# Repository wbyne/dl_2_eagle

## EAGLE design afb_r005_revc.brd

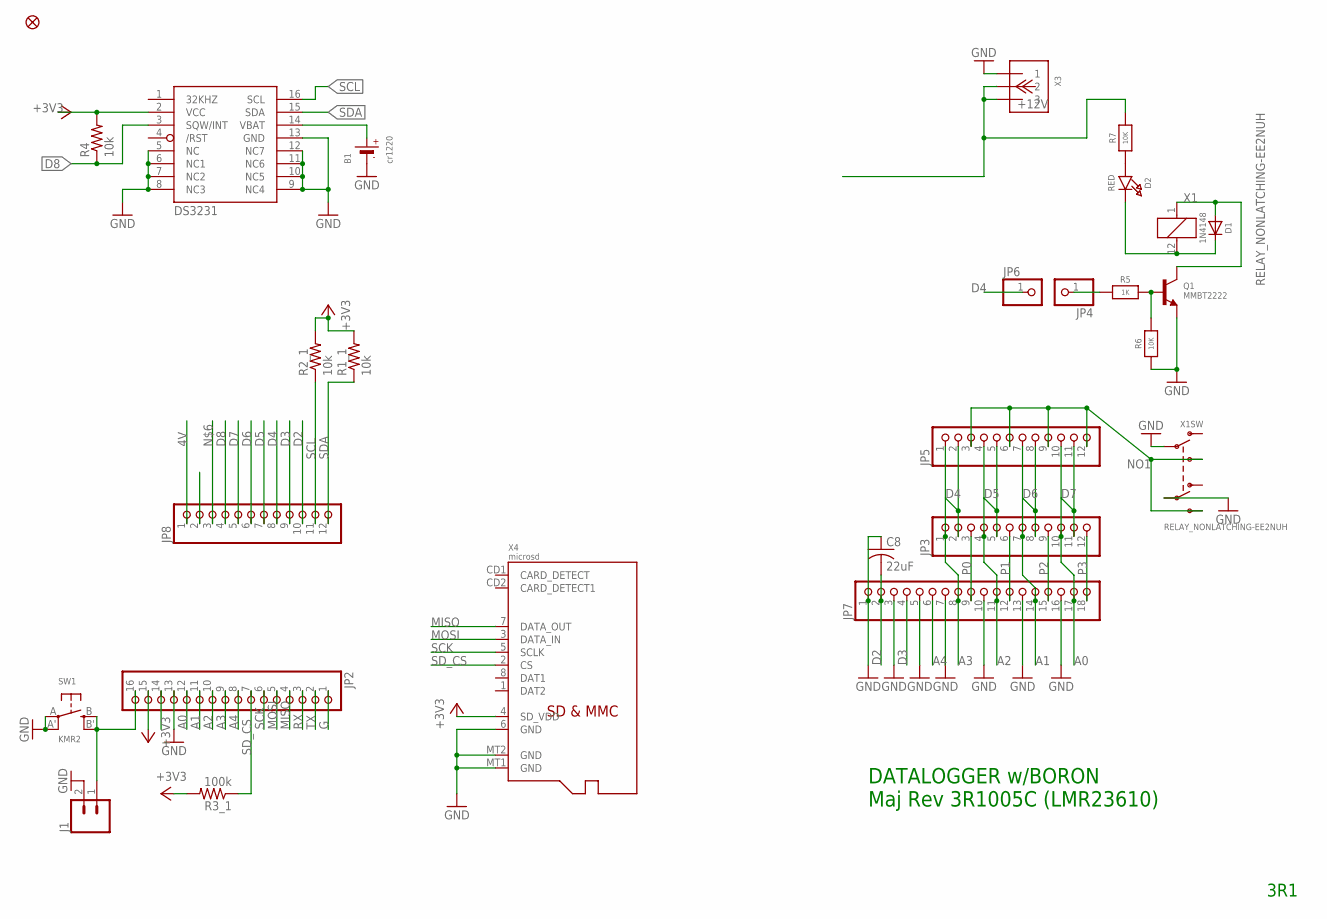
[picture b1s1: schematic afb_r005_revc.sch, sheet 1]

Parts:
B1: cr1220; CR1220-2
C8: 22uF; C0805
D1: 1N4148; SOD-323
D2: RED; CHIPLED_0805_NOOUTLINE
FID1: FIDUCIAL_1MM
IC2: DS3231/SO; SO16W
J1: CONN_02; 1X02
JP2: HEADER-1X16ROUND; 1X16_ROUND
JP3, JP5, JP8: PINHD-1X12-CB; 1X12-CB
JP4, JP6: HEADER-1X1ROUND; 1X01_ROUND
JP7: PINHD-1X18; 1X18
Q1: MMBT2222; SOT23-R
R1_1, R2_1, R4: 10k; R0805
R3_1: 100k; R0805
R5: 1K; 0805-NO
R6, R7: 10K; 0805-NO
SW1: KMR2; BTN_KMR2_4.6X2.8
X1: RELAY_NONLATCHING-EE2NUH; RELAY_EE2_NOLATCH
X3: TERMBLOCK_1X3; TERMBLOCK_1X3-3.5MM
X4: microsd; MICROSD

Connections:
4V: JP8.1; also elsewhere on the board
+3V3: IC2.2 (VCC), JP2.15, R1_1.2, R2_1.2, R3_1.2, R4.2, X4.4 (SD_VDD)
A0: JP2.12, JP3.10, JP5.10, JP7.17
A1: JP2.11, JP3.7, JP5.7, JP7.14
A2: JP2.10, JP3.4, JP5.4, JP7.11
A3: JP2.9, JP3.1, JP5.1, JP7.8
A4: JP2.8, JP7.6
AREF: JP2.14
D2: C8.2, JP7.2, JP8.10
D3: JP7.4, JP8.9
D4: JP3.2, JP5.2, JP6.1, JP8.8
D5: JP3.5, JP5.5, JP8.7
D6: JP3.8, JP5.8, JP8.6
D7: JP3.11, JP5.11, JP8.5
D8: IC2.3 (SQW/INT), JP8.4, R4.1
G: JP2.1
GND: B1.-, C8.1, IC2.5 (NC), IC2.6 (NC1), IC2.7 (NC2), IC2.8 (NC3), IC2.9 (NC4), IC2.10 (NC5), IC2.11 (NC6), IC2.12 (NC7), IC2.13 (GND), J1.2, JP2.13, JP7.1, JP7.3, JP7.5, JP7.7, JP7.10, JP7.13, JP7.16, Q1.2 (E), R6.1, SW1.A, SW1.A' (P1), X1.4 (P2), X1.9 (P1), X3.1, X4.6 (GND), X4.MT1 (GND), X4.MT2 (GND); also elsewhere on the board
MISO: JP2.4, X4.7 (DATA_OUT)
MOSI: JP2.5, X4.3 (DATA_IN)
unnamed: B1.+, IC2.14 (VBAT)
unnamed: D1.A, Q1.3 (C), X1.1
unnamed: D1.C, D2.C, X1.12 (2)
unnamed: Q1.1 (B), R5.2, R6.2
unnamed: JP4.1, R5.1
unnamed: D2.A, R7.1
NO1: JP5.3, JP5.6, JP5.9, JP5.12, X1.5 (S2), X1.8 (S1)
P0: JP3.3, JP7.9
P1: JP3.6, JP7.12
P2: JP3.9, JP7.15
P3: JP3.12, JP7.18
RESET: J1.1, JP2.16, SW1.B (S), SW1.B' (S1)
RX: JP2.3
SCK: JP2.6, X4.5 (SCLK)
SCL: IC2.16 (SCL), JP8.11, R2_1.1
SDA: IC2.15 (SDA), JP8.12, R1_1.1
SD_CS: JP2.7, R3_1.1, X4.2 (CS)
TX: JP2.2
VIN: R7.2, X3.2, X3.3; also elsewhere on the board

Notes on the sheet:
DATALOGGER w/BORON Maj Rev 3R1005C (LMR23610)
3R1

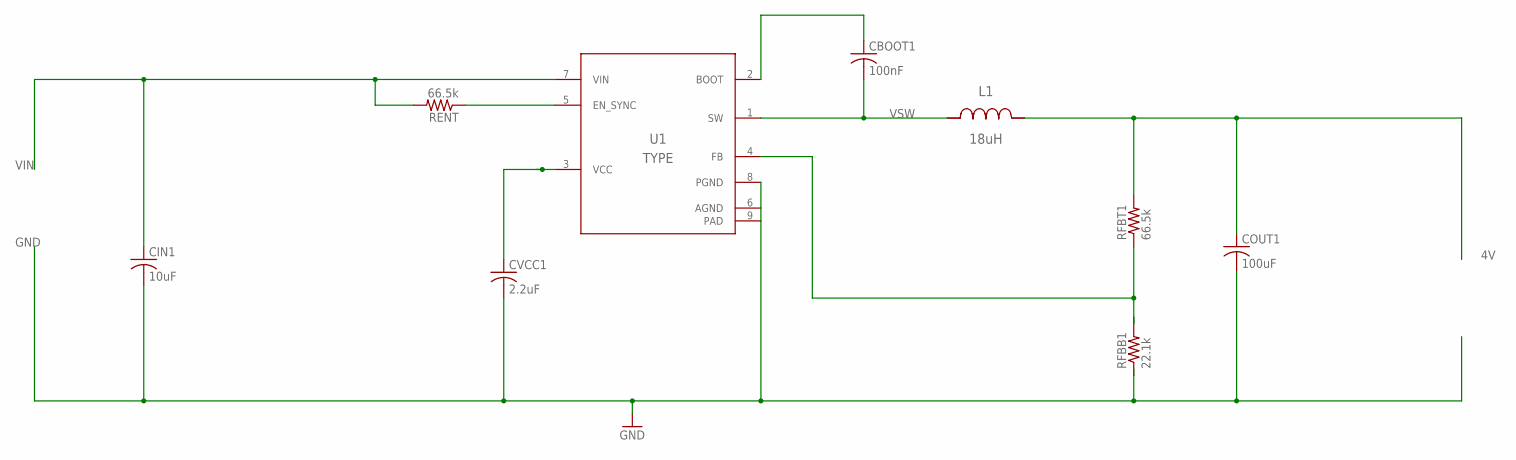
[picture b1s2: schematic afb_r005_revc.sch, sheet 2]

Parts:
CBOOT1: 100nF; C0805
CIN1: 10uF; C0805
COUT1: 100uF; C3216
CVCC1: 2.2uF; C0805
L1: 18uH; IND_NPI54C
RENT: 66.5k; R0805
RFBB1: 22.1k; R0805
RFBT1: 66.5k; R0805
U1: Value; DDA0008E_N

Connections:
3: CVCC1.1, U1.3 (VCC)
4: CBOOT1.1, U1.2 (BOOT)
4V: COUT1.1, L1.2, RFBT1.2; also elsewhere on the board
FB: RFBB1.2, RFBT1.1, U1.4 (FB)
GND: CIN1.2, COUT1.2, CVCC1.2, RFBB1.1, U1.6 (AGND), U1.8 (PGND), U1.9 (PAD); also elsewhere on the board
unnamed: RENT.1, U1.5 (EN_SYNC)
VIN: CIN1.1, RENT.2, U1.7 (VIN); also elsewhere on the board
VSW: CBOOT1.2, L1.1, U1.1 (SW)

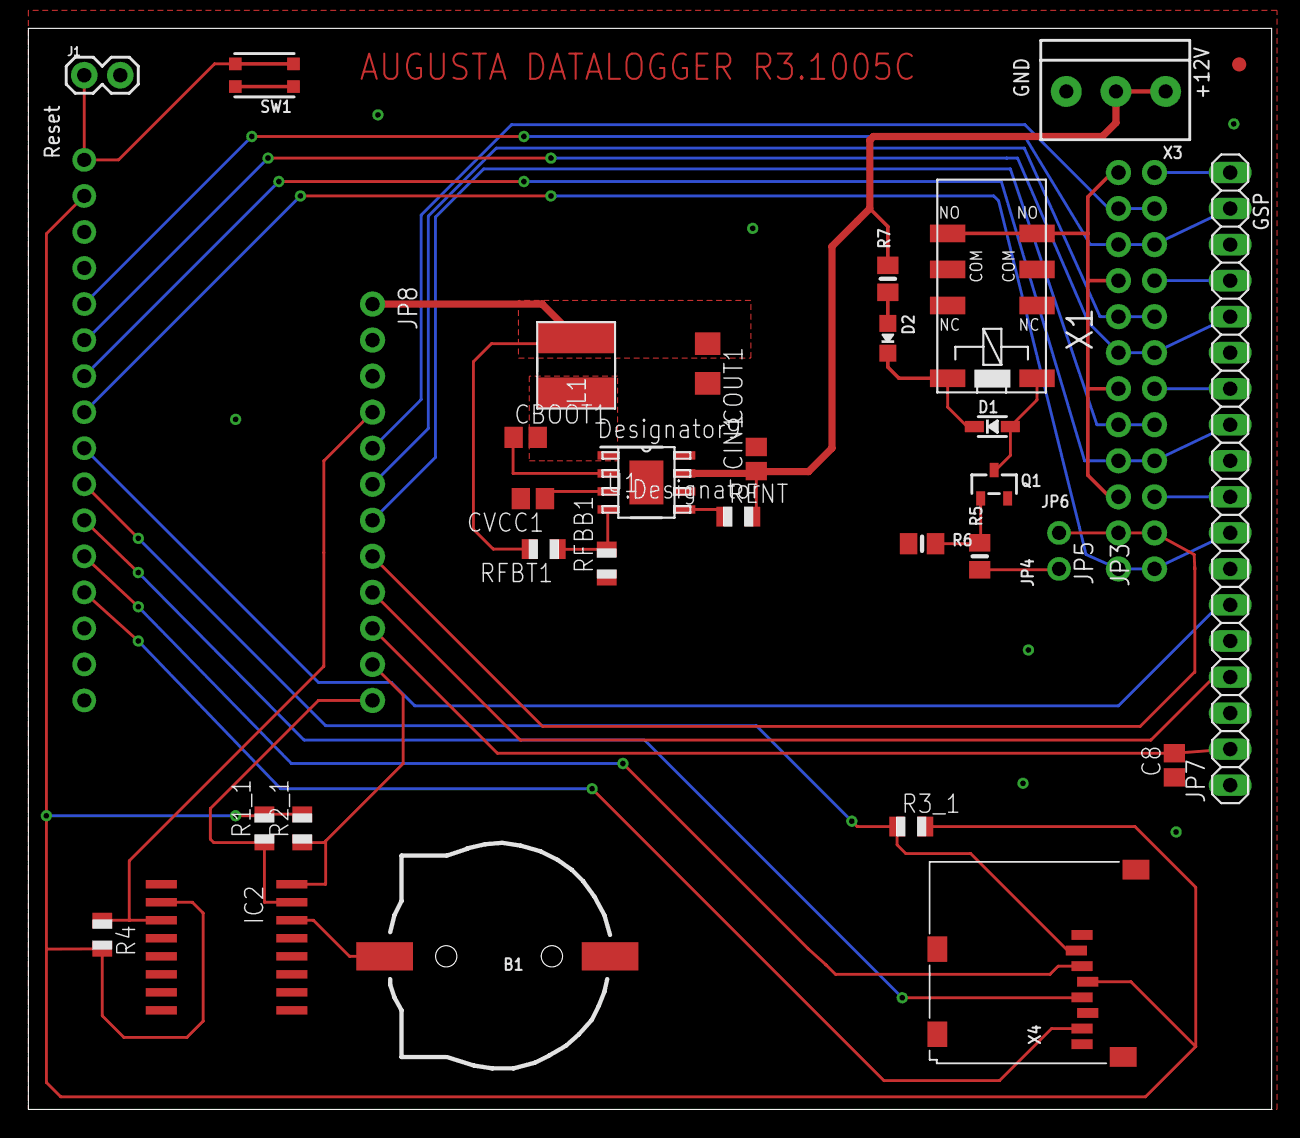
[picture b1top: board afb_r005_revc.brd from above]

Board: 2 copper layers, 87.6 x 76.2 mm, 35 parts (0 on the bottom side), 39 nets.

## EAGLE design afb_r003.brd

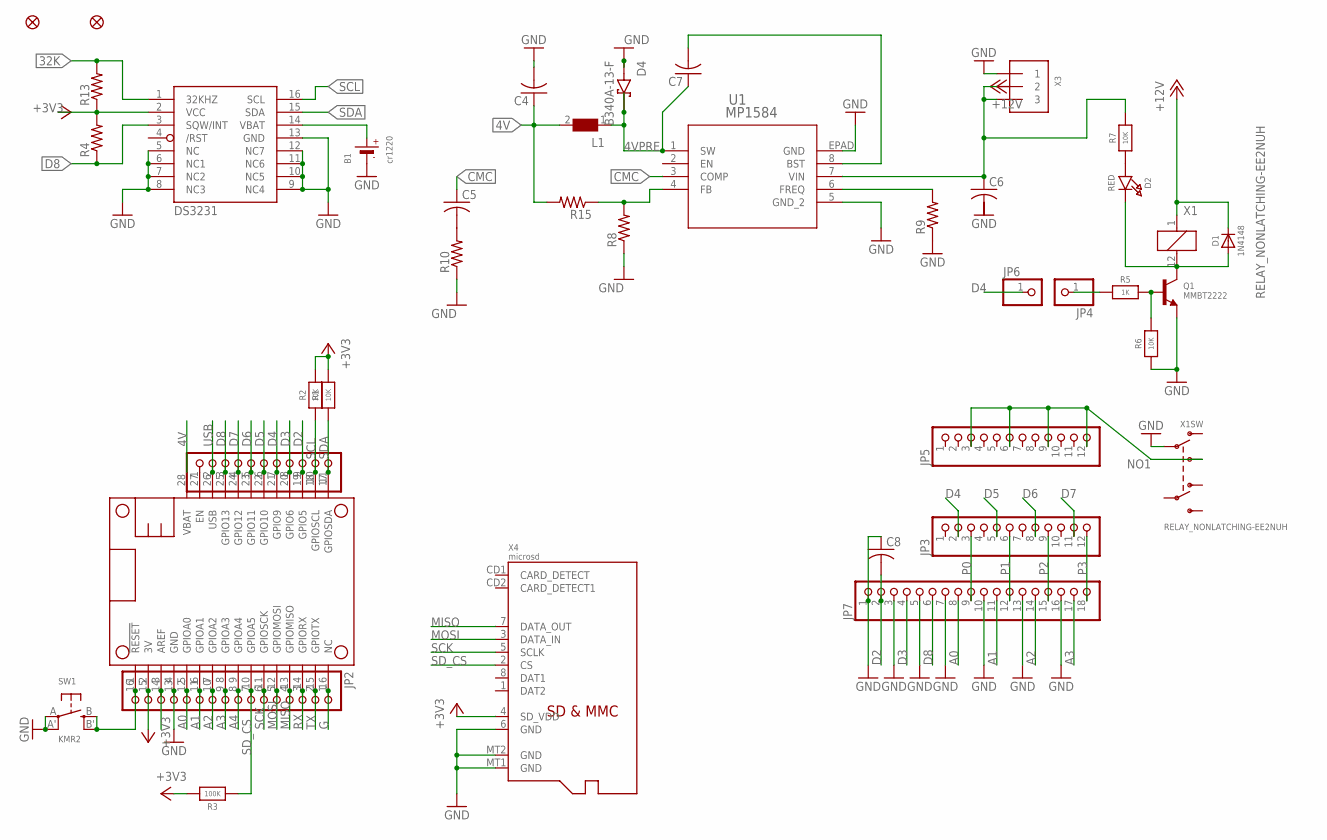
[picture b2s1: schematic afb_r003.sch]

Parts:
B1: cr1220; CR1220-2
C4, C5, C6, C7, C8: C-USC0805; C0805
D1: 1N4148; SOD-323
D2: RED; CHIPLED_0805_NOOUTLINE
D4: B340A-13-F; DIOM5226X240N
FID1, FID2: FIDUCIAL_1MM
IC2: DS3231/SO; SO16W
JP1: HEADER-1X11; 1X11_ROUND
JP2: HEADER-1X16ROUND; 1X16_ROUND
JP3, JP5: PINHD-1X12-CB; 1X12-CB
JP4, JP6: HEADER-1X1ROUND; 1X01_ROUND
JP7: PINHD-1X18; 1X18
L1: WE-PD-744771115_1260/1245/1280/1210; WE-PD_1260/1245/1280/1210
MS1: FEATHERWING_NODIM
Q1: MMBT2222; SOT23-R
R1, R2: 10K; 0603-NO
R3: 100K; 0603-NO
R4, R8, R9, R10, R13, R15: R-US_R0805; R0805
R5: 1K; 0805-NO
R6, R7: 10K; 0805-NO
SW1: KMR2; BTN_KMR2_4.6X2.8
U1: MP1584; SOIC8E_MPS
X1: RELAY_NONLATCHING-EE2NUH; RELAY_EE2_NOLATCH
X3: TERMBLOCK_1X3; TERMBLOCK_1X3-3.5MM
X4: microsd; MICROSD

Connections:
4V: C4.1, L1.2, MS1.28 (VBAT), R15.2
4VPRE: C7.1, D4.C, L1.1, U1.1 (SW)
32K: IC2.1 (32KHZ), R13.2
+3V3: JP2.15, MS1.2 (3V), R1.2, R2.2, R3.2, X4.4 (SD_VDD)
+12V: D1.C, X1.1
A0: JP2.12, JP7.8, MS1.5 (GPIOA0)
A1: JP2.11, JP7.11, MS1.6 (GPIOA1)
A2: JP2.10, JP7.14, MS1.7 (GPIOA2)
A3: JP2.9, JP7.17, MS1.8 (GPIOA3)
A4: JP2.8, MS1.9 (GPIOA4)
AREF: JP2.14, MS1.3 (AREF)
BSC: C7.2, U1.8 (BST)
CMC: C5.1, U1.3 (COMP)
D2: C8.2, JP1.9, JP7.2, MS1.19 (GPIO5)
D3: JP1.8, JP7.4, MS1.20 (GPIO6)
D4: JP1.7, JP3.2, JP6.1, MS1.21 (GPIO9)
D5: JP1.6, JP3.5, MS1.22 (GPIO10)
D6: JP1.5, JP3.8, MS1.23 (GPIO11)
D7: JP1.4, JP3.11, MS1.24 (GPIO12)
D8: IC2.2 (VCC), JP1.3, JP7.6, MS1.25 (GPIO13), R4.2, R13.1
EN: JP1.1, MS1.27 (EN)
G: JP2.1, MS1.16 (NC)
GND: B1.-, C4.2, C8.1, D4.A, IC2.5 (NC), IC2.6 (NC1), IC2.7 (NC2), IC2.8 (NC3), IC2.9 (NC4), IC2.10 (NC5), IC2.11 (NC6), IC2.12 (NC7), IC2.13 (GND), JP2.13, JP7.1, JP7.3, JP7.5, JP7.7, JP7.10, JP7.13, JP7.16, MS1.4 (GND), Q1.2 (E), R6.1, R8.1, R9.1, R10.1, SW1.A, SW1.A' (P1), U1.5 (GND_2), U1.EPAD (GND), X1.9 (P1), X3.1, X4.6 (GND), X4.MT1 (GND), X4.MT2 (GND)
MISO: JP2.4, MS1.13 (GPIOMISO), X4.7 (DATA_OUT)
MOSI: JP2.5, MS1.12 (GPIOMOSI), X4.3 (DATA_IN)
unnamed: B1.+, IC2.14 (VBAT)
unnamed: D1.A, D2.C, Q1.3 (C), X1.12 (2)
unnamed: R8.2, R15.1, U1.4 (FB)
unnamed: C5.2, R10.2
unnamed: C6.1, R7.2, U1.7 (VIN), X3.2, X3.3
unnamed: IC2.3 (SQW/INT), R4.1
unnamed: R9.2, U1.6 (FREQ)
unnamed: Q1.1 (B), R5.2, R6.2
unnamed: JP4.1, R5.1
unnamed: D2.A, R7.1
NO1: JP5.3, JP5.6, JP5.9, JP5.12, X1.8 (S1)
P0: JP3.3, JP7.9
P1: JP3.6, JP7.12
P2: JP3.9, JP7.15
P3: JP3.12, JP7.18
RESET: JP2.16, MS1.1 (!RESET), SW1.B (S), SW1.B' (S1)
RX: JP2.3, MS1.14 (GPIORX)
SCK: JP2.6, MS1.11 (GPIOSCK), X4.5 (SCLK)
SCL: IC2.16 (SCL), JP1.10, MS1.18 (GPIOSCL), R2.1
SDA: IC2.15 (SDA), JP1.11, MS1.17 (GPIOSDA), R1.1
SD_CS: JP2.7, MS1.10 (GPIOA5), R3.1, X4.2 (CS)
TX: JP2.2, MS1.15 (GPIOTX)
USB: JP1.2, MS1.26 (USB)

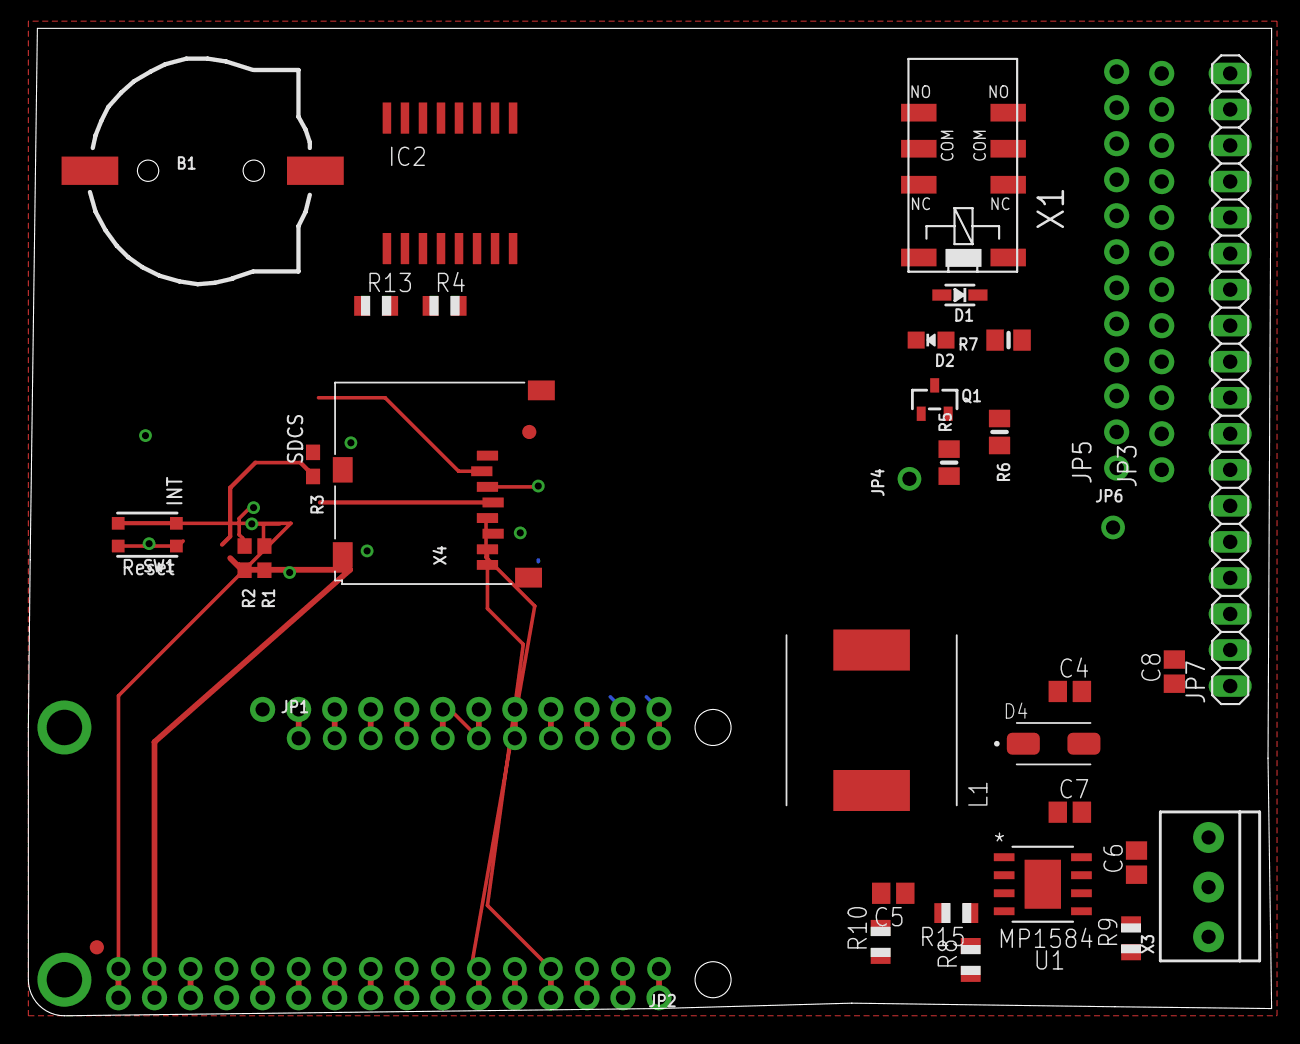
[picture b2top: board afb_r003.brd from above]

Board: 2 copper layers, 87.6 x 69.6 mm, 41 parts (0 on the bottom side), 48 nets.

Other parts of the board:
U$4: ADAFRUIT_3.5MM
U$5: PCBFEAT-REV-040

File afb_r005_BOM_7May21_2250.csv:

"Part";"Value";"Device";"Package";"Description";"AVAILABILITY";"BOM";"BUILT_BY";"COPYRIGHT";"DATASHEET";"DESCRIPTION";"DIGI-KEY_PART_NUMBER";"MANUFACTURER_PART_NUMBER";"MF";"MP";"MPN";"OC_FARNELL";"OC_NEWARK";"PACKAGE";"PRICE";"PURCHASE-URL";"SOURCELIBRARY";"SUPPLIER";"VENDOR";
"B1";"cr1220";"BATTERYCR1220_2";"CR1220-2";"CR1220 SMT - Digikey: 3001K-ND";"";"";"";"";"";"";"";"";"";"";"";"";"";"";"";"";"";"";"";
"C4";"22uF";"C-USC0805";"C0805";"CAPACITOR, American symbol";"";"";"";"";"";"";"";"";"";"";"";"";"";"";"";"";"";"";"";
"C5";"200pF";"C-USC0805";"C0805";"CAPACITOR, American symbol";"";"";"";"";"";"";"";"";"";"";"";"";"";"";"";"";"";"";"";
"C6";"10uF";"C-USC0805";"C0805";"CAPACITOR, American symbol";"";"";"";"";"";"";"";"";"";"";"";"";"";"";"";"";"";"";"";
"C7";"100nF";"C-USC0805";"C0805";"CAPACITOR, American symbol";"";"";"";"";"";"";"";"";"";"";"";"";"";"";"";"";"";"";"";
"C8";"";"C-USC0805";"C0805";"CAPACITOR, American symbol";"";"";"";"";"";"";"";"";"";"";"";"";"";"";"";"";"";"";"";
"D1";"1N4148";"DIODESOD-323";"SOD-323";"Diode";"";"";"";"";"";"";"";"";"";"";"";"";"";"";"";"";"";"";"";
"D2";"RED";"LED0805_NOOUTLINE";"CHIPLED_0805_NOOUTLINE";"LED";"";"";"";"";"";"";"";"";"";"";"";"";"";"";"";"";"";"";"";
"D4";"B340A-13-F";"B340A-13-F";"DIOM5226X240N";"Diode, Rectifier, 3a, 40v, Do-214ac, Full Reel";"";"";"";"";"";" Diode Schottky 40V 3A Surface Mount SMA ";"B340A-FDICT-ND";"";"Diodes Inc.";"B340A-13-F";"";"";"";"DO-214 Diodes Inc.";"";"https://pricing.snapeda.com/search/part/B340A-13-F/?ref=eda";"";"";"";
"FID1";"FIDUCIAL_1MM";"FIDUCIAL_1MM";"FIDUCIAL_1MM";"Fiducial Alignment Points";"";"EXCLUDE";"";"";"";"";"";"";"";"";"";"";"";"";"";"";"";"";"";
"IC2";"DS3231/SO";"DS3231/SO";"SO16W";"";"Unavailable";"";"";"";"";" Real Time Clock (RTC) IC Clock/Calendar I²C, 2-Wire Serial 16-SOIC (0.295, 7.50mm Width) ";"";"";"Maxim Integrated";"DS3231";"";"";"";"SOIC-16 Maxim Integrated";"None";"";"";"";"";
"JP2";"";"HEADER-1X16ROUND";"1X16_ROUND";"PIN HEADER";"";"";"";"";"";"";"";"";"";"";"";"";"";"";"";"";"";"";"";
"JP3";"";"PINHD-1X12-CB";"1X12-CB";"PIN HEADER";"";"";"";"";"";"";"";"";"";"";"";"";"";"";"";"";"";"";"";
"JP4";"";"HEADER-1X1ROUND";"1X01_ROUND";"PIN HEADER";"";"";"";"";"";"";"";"";"";"";"";"";"";"";"";"";"";"";"";
"JP5";"";"PINHD-1X12-CB";"1X12-CB";"PIN HEADER";"";"";"";"";"";"";"";"";"";"";"";"";"";"";"";"";"";"";"";
"JP6";"";"HEADER-1X1ROUND";"1X01_ROUND";"PIN HEADER";"";"";"";"";"";"";"";"";"";"";"";"";"";"";"";"";"";"";"";
"JP7";"";"PINHD-1X18";"1X18";"PIN HEADER";"";"";"";"";"";"";"";"";"";"";"";"";"";"";"";"";"";"";"";
"JP8";"";"PINHD-1X12-CB";"1X12-CB";"PIN HEADER";"";"";"";"";"";"";"";"";"";"";"";"";"";"";"";"";"";"";"";
"L1";"15uH";"WE-PD-744771115_1260/1245/1280/1210";"WE-PD_1260/1245/1280/1210";"SMD-Shielded Power Inductors WE-PD";"";"";"";"";"";"";"";"";"";"";"744771115";"1635908";"08P2786";"1260";"";"";"";"Wuerth Elektronik";"";
"Q1";"MMBT2222";"TRANSISTOR_NPN";"SOT23-R";"NPN Transistor";"";"";"";"";"";"";"";"";"";"";"";"";"";"";"";"";"";"";"";
"R1";"10K";"RESISTOR_0603_NOOUT";"0603-NO";"Resistors";"";"";"";"";"";"";"";"";"";"";"";"";"";"";"";"";"";"";"";
"R2";"10K";"RESISTOR_0603_NOOUT";"0603-NO";"Resistors";"";"";"";"";"";"";"";"";"";"";"";"";"";"";"";"";"";"";"";
"R3";"100K";"RESISTOR_0603_NOOUT";"0603-NO";"Resistors";"";"";"";"";"";"";"";"";"";"";"";"";"";"";"";"";"";"";"";
"R4";"10k";"R-US_R0805";"R0805";"RESISTOR, American symbol";"";"";"";"";"";"";"";"";"";"";"";"";"";"";"";"";"";"";"";
"R5";"1K";"RESISTOR0805_NOOUTLINE";"0805-NO";"Resistors";"";"";"";"";"";"";"";"";"";"";"";"";"";"";"";"";"";"";"";
"R6";"10K";"RESISTOR0805_NOOUTLINE";"0805-NO";"Resistors";"";"";"";"";"";"";"";"";"";"";"";"";"";"";"";"";"";"";"";
"R7";"10K";"RESISTOR0805_NOOUTLINE";"0805-NO";"Resistors";"";"";"";"";"";"";"";"";"";"";"";"";"";"";"";"";"";"";"";
"R8";"40.2k";"R-US_R0805";"R0805";"RESISTOR, American symbol";"";"";"";"";"";"";"";"";"";"";"";"";"";"";"";"";"";"";"";
"R9";"360k";"R-US_R0805";"R0805";"RESISTOR, American symbol";"";"";"";"";"";"";"";"";"";"";"";"";"";"";"";"";"";"";"";
"R10";"63.96k";"R-US_R0805";"R0805";"RESISTOR, American symbol";"";"";"";"";"";"";"";"";"";"";"";"";"";"";"";"";"";"";"";
"R15";"162k";"R-US_R0805";"R0805";"RESISTOR, American symbol";"";"";"";"";"";"";"";"";"";"";"";"";"";"";"";"";"";"";"";
"SW1";"KMR2";"SWITCH_TACT_SMT4.6X2.8";"BTN_KMR2_4.6X2.8";"SMT Tact Switches";"";"";"";"";"";"";"";"";"";"";"";"";"";"";"";"";"";"";"";
"U1";"MP1584";"MP1584";"SOIC8E_MPS";"";"";"";"EMA_Cory";"Copyright (C) 2018 Accelerated Designs. All rights reserved";"https://www.monolithicpower.com/en/documentview/productdocum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";"";"";"MP1584";"";"";"";"";"";"";"";"";"MPS_2020-01-27";"";"Monolithic Power Systems Inc";
"X1";"RELAY_NONLATCHING-EE2NUH";"RELAY_NONLATCHING-EE2NUH";"RELAY_EE2_NOLATCH";"";"";"";"";"";"";"";"";"";"";"";"";"";"";"";"";"";"";"";"";
"X3";"";"TERMBLOCK_1X3";"TERMBLOCK_1X3-3.5MM";"3.5mm Terminal block";"";"";"";"";"";"";"";"";"";"";"";"";"";"";"";"";"";"";"";
"X4";"microsd";"MICROSD";"MICROSD";"MicroSD/Transflash Card Holder with SPI pinout";"";"";"";"";"";"";"";"";"";"";"";"";"";"";"";"";"";"";"";

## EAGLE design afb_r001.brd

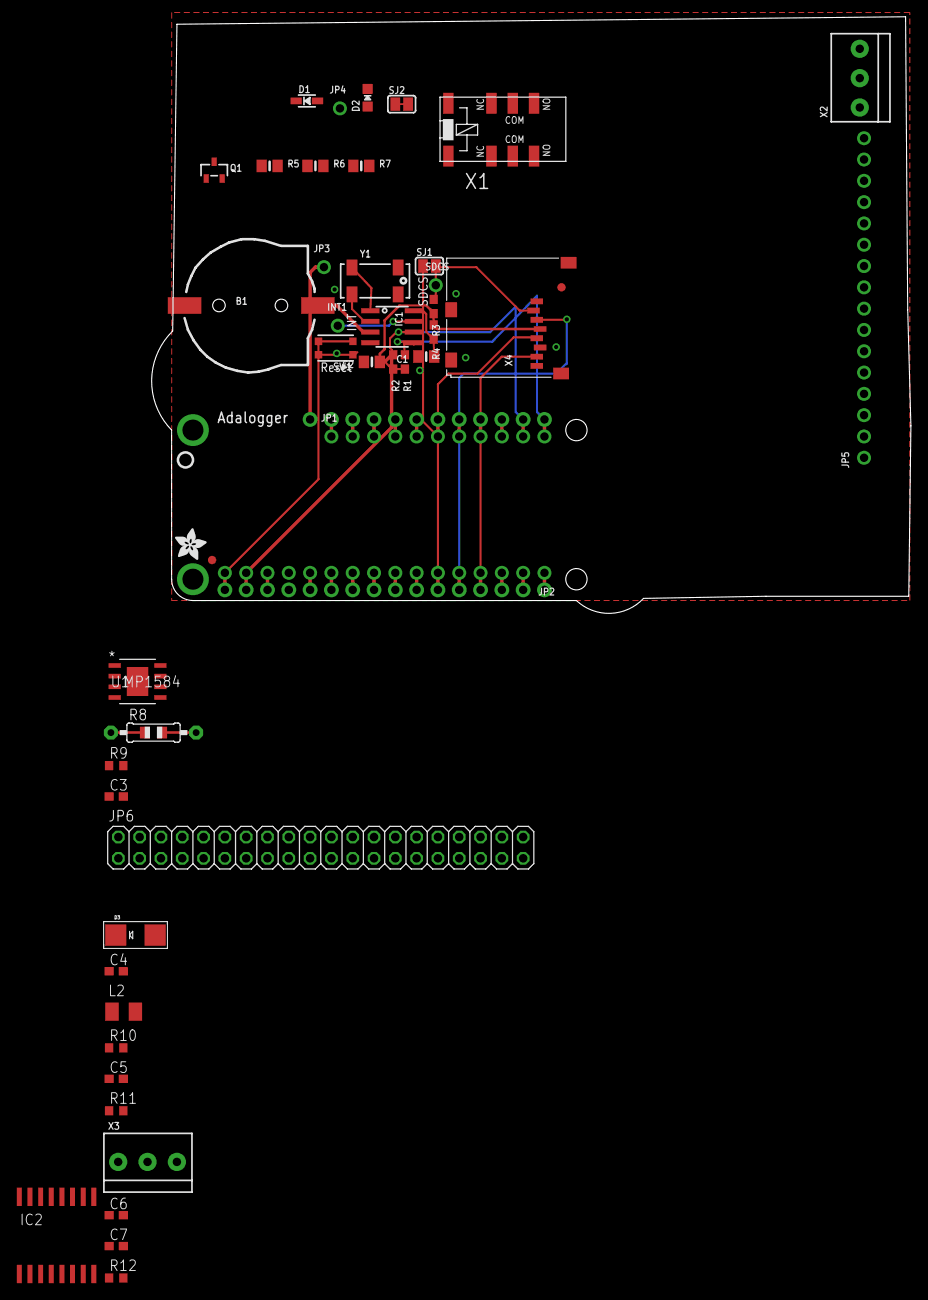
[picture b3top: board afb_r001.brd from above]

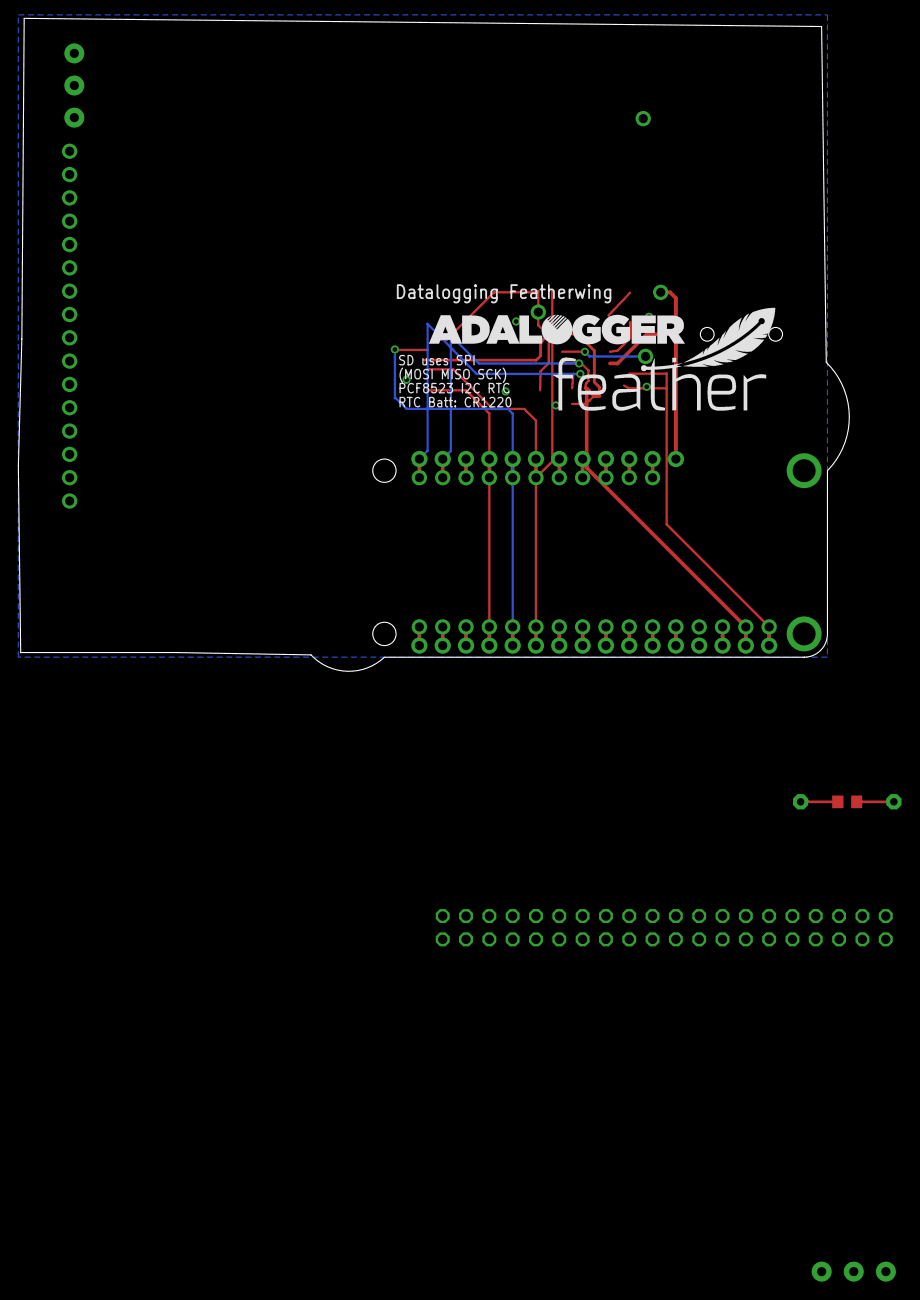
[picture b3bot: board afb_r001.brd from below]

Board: 2 copper layers, 90.5 x 71.1 mm, 51 parts (2 on the bottom side), 50 nets.

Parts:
B1: cr1220; CR1220-2
C1, C2: 10uF; 0805-NO
C3, C4, C5, C6, C7: C0603
D1: 1N4148; SOD-323
D2: RED; CHIPLED_0805_NOOUTLINE
D3: SMADIODE
FID1, FID2: FIDUCIAL_1MM
IC1: PCF8523T; SOIC8_150MIL
IC2: DS3231/SO; SO16W
INT1: 1X01_ROUND
JP1: 1X11_ROUND
JP2, JP5: 1X16_ROUND
JP3, JP4: 1X01_ROUND
JP6: 2X20
L2: L3225M
MS1: FEATHERWING_NODIM
Q1: MMBT2222; SOT23-R
R1, R2: 10K; 0603-NO
R3: 100K; 0603-NO
R4: 1K; 0603-NO
R5, R7: 1K; 0805-NO
R6: 10K; 0805-NO
R8: 0805-THM
R9, R10, R11, R12: R0603
SDCS: 1X01_ROUND
SJ1, SJ2: SOLDERJUMPER_CLOSEDWIRE
SW1: KMR2; BTN_KMR2_4.6X2.8
U1: MP1584; SOIC8E_MPS
U$2: FEATHERLOGO
U$3: ADALOGGER_LOGO
U$4: ADAFRUIT_3.5MM
U$5: PCBFEAT-REV-040
X1: RELAY_NONLATCHING-EE2NUH; RELAY_EE2_NOLATCH
X2, X3: TERMBLOCK_1X3-3.5MM
X4: microsd; MICROSD
Y1: 32khz; CRYSTAL_8X3.8

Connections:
3.3V: D1.C, R7.2, X1.1
4V: C4.1, C7.1, D3.C, L2.1, L2.2, R8.2, U1.1
+3V3: C2.1, IC2.2, JP2.15, MS1.2, R1.2, R2.2, R3.2, R4.1, X4.4
A: JP2.12, MS1.5
AREF: JP2.14, MS1.3
B: JP2.11, MS1.6
C: JP2.10, MS1.7
CMC: C3.1, C5.1, U1.3
COM1: X1.9, X2.2
CR1220: B1.+, IC1.3, IC2.14
CS: JP1.6, MS1.22, SJ1.1
D: JP2.9, MS1.8
E: JP2.8, MS1.9
EN: JP1.1, MS1.27
ENC: R12.2, U1.2
F: JP2.7, MS1.10
G: JP2.1, MS1.16
GND: B1.-, C1.2, C2.2, C4.2, C5.2, D3.A, IC1.4, IC2.13, JP2.13, MS1.4, Q1.2, R6.1, R9.1, R10.1, R11.1, SW1.A, SW1.A', U1.5, U1.EPAD, X3.1, X4.6, X4.MT1, X4.MT2
H: JP1.9, MS1.19
I: JP1.8, MS1.20
INT1: IC1.7, INT1.1
J: JP1.7, MS1.21
L: JP1.5, MS1.23
M: JP1.4, MS1.24
MISO: JP2.4, MS1.13, X4.7
MOSI: JP2.5, MS1.12, X4.3
N: JP1.3, MS1.25
unnamed: C1.1, IC1.8, R4.2
unnamed: D1.A, Q1.3, SJ2.1, X1.12
unnamed: R8.1, R9.2, U1.4
unnamed: C3.2, R10.2
unnamed: C6.1, R12.1, U1.7, X3.2, X3.3
unnamed: IC1.1, Y1.P$4
unnamed: IC1.2, Y1.P$1
unnamed: R11.2, U1.6
unnamed: Q1.1, R5.2, R6.2
unnamed: JP4.1, R5.1
unnamed: D2.C, SJ2.2
unnamed: D2.A, R7.1
unnamed: X1.10, X2.3
NO1: X1.8, X2.1
RESET: JP2.16, MS1.1, SW1.B, SW1.B'
RX: JP2.3, MS1.14
SCK: JP2.6, MS1.11, X4.5
SCL: IC1.6, JP1.10, MS1.18, R2.1
SDA: IC1.5, JP1.11, MS1.17, R1.1
SD_CS: R3.1, SDCS.1, SJ1.2, X4.2
TX: JP2.2, MS1.15
USB: JP1.2, MS1.26
VBAT: JP3.1, MS1.28

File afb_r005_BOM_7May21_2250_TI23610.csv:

Component,Supplier,Part_No,Value,Type,Size,Item,Part,Part_Source,,Schematic_Part,Value,Device,Package,Description,AVAILABILITY,BOM,BUILT_BY,COPYRIGHT,DATASHEET,DESCRIPTION,DIGI-KEY_PART_NUMBER,MANUFACTURER_PART_NUMBER,MF,MP,MPN,OC_FARNELL,OC_NEWARK,PACKAGE,PRICE,PURCHASE-URL,SOURCELIBRARY,SUPPLIER,VENDOR
RTC,Mouser,855-S8411-45R ,,SMD,,CR1120 SMD Coin Cell holder,B1,Schematic,,B1,cr1220,BATTERYCR1220_2,CR1220-2,CR1220 SMT - Digikey: 3001K-ND,,,,,,,,,,,,,,,,,,,
Relay_Assy,Mouser,512-1N4148,1N4148,,,,,Schematic,,D1,1N4148,DIODESOD-323,SOD-323,Diode,,,,,,,,,,,,,,,,,,,
Relay_Assy,Mouser,SML-H12U8TT86C ,,,,,,,,D2,RED,LED0805_NOOUTLINE,CHIPLED_0805_NOOUTLINE,LED,,,,,,,,,,,,,,,,,,,
RTC,Mouser,700-DS3231S#,DS3231,SMD,,,DS3231,Schematic,,IC2,DS3231/SO,DS3231/SO,SO16W,,Unavailable,,,,," Real Time Clock (RTC) IC Clock/Calendar I²C, 2-Wire Serial 16-SOIC (0.295, 7.50mm Width) ",,,Maxim Integrated,DS3231,,,,SOIC-16 Maxim Integrated,None,,,,
Feather_Mount,Mouser/Adafruit,485-2830 ,,,,12pin/16pin Stacking Headers for Feather,JP2/JP8,Schematic,,JP2,,HEADER-1X16ROUND,1X16_ROUND,PIN HEADER,,,,,,,,,,,,,,,,,,,
,Mouser/Adafruit,485-392,,,,10 Pack of Male Headers,,,,JP3-7,,PINHD-1X12-CB,1X12-CB,PIN HEADER,,,,,,,,,,,,,,,,,,,
Feather_Mount,Mouser/Adafruit,485-2830 ,,,,12pin/16pin Stacking Headers for Feather,JP2/JP8,Schematic,,JP8,,PINHD-1X12-CB,1X12-CB,PIN HEADER,,,,,,,,,,,,,,,,,,,
Relay_assy,Mouser,863-NSVMMBT2222AM3T5,,,,,,,,Q1,MMBT2222,TRANSISTOR_NPN,SOT23-R,NPN Transistor,,,,,,,,,,,,,,,,,,,
SCL_Pullup,Mouser,,10k,,,,R1,Schematic,,R1,10K,RESISTOR_0603_NOOUT,0603-NO,Resistors,,,,,,,,,,,,,,,,,,,
SDA_Pullup,Mouser,,10k,,,,R2,Schematic,,R2,10K,RESISTOR_0603_NOOUT,0603-NO,Resistors,,,,,,,,,,,,,,,,,,,
SD_CS_Pullup,Mouser,,100k,,,,R3,Schematic,,R3,100K,RESISTOR_0603_NOOUT,0603-NO,Resistors,,,,,,,,,,,,,,,,,,,
RTC,Mouser,71-CRCW080510K0JNEAC,10k,SMD,,,R4,Schematic,,R4,10k,R-US_R0805,R0805,"RESISTOR, American symbol",,,,,,,,,,,,,,,,,,,
Relay_assy,Mouser,71-CRCW08051K00JNEAC,,,,,,,,R5,1K,RESISTOR0805_NOOUTLINE,0805-NO,Resistors,,,,,,,,,,,,,,,,,,,
Relay_assy,Mouser,71-CRCW080510K0JNEAC,,,,,,,,R6,10K,RESISTOR0805_NOOUTLINE,0805-NO,Resistors,,,,,,,,,,,,,,,,,,,
Relay_assy,Mouser,71-CRCW080510K0JNEAC,,,,,,,,R7,10K,RESISTOR0805_NOOUTLINE,0805-NO,Resistors,,,,,,,,,,,,,,,,,,,
Feather_Mount,Mouser,612-TL6330AF200Q ,,,,SWITCH_TACT_SMT4.6X2.8 (SWITCH_TACT_SMT),,,,SW1,KMR2,SWITCH_TACT_SMT4.6X2.8,BTN_KMR2_4.6X2.8,SMT Tact Switches,,,,,,,,,,,,,,,,,,,
Relay_assy,Digikey,399-11000-1-ND - Cut Tape (CT),,,,,,,,X1,RELAY_NONLATCHING-EE2NUH,RELAY_NONLATCHING-EE2NUH,RELAY_EE2_NOLATCH,,,,,,,,,,,,,,,,,,,,
Power_Supply,Mouser,651-1071011 ,,,,,,,,X3,,TERMBLOCK_1X3,TERMBLOCK_1X3-3.5MM,3.5mm Terminal block,,,,,,,,,,,,,,,,,,,
SD_Card,Mouser,538-47352-1001 ,,,,,,,,X4,microsd,MICROSD,MICROSD,MicroSD/Transflash Card Holder with SPI pinout,,,,,,,,,,,,,,,,,,,
SD_CS_Pullup,,652-CMP0805AFX-1003L ,,,,,R3,,,,100K,RESISTOR0805_NOOUTLINE,,,,,,,,,,,,,,,,,,,,,
SCL_Pullup,,71-CRCW080510K0JNEAC,,,,,R1,,,,10K,RESISTOR0805_NOOUTLINE,,,,,,,,,,,,,,,,,,,,,
SDA_Pullup,,71-CRCW080510K0JNEAC,,,,,R2,,,,10K,RESISTOR0805_NOOUTLINE,,,,,,,,,,,,,,,,,,,,,

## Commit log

2021-04-27 initial_commit
2021-05-06 added R4 modifications and changed name to major rev 3. Need to clean up my naming.
2021-05-13 Addition of Rev3.1005C, using TI2361 regulator

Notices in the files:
parts and their libraries:
COPYRIGHT: Copyright (C) 2018 Accelerated Designs. All rights reserved
SparkFun-Connectors: Licensing: Creative Commons ShareAlike 4.0 International - https://creativecommons.org/licenses/by-sa/4.0
